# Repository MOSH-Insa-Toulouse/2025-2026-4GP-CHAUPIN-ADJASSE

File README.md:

##### **Promotion 2025-2026 Génie Physique INSA TOulouse** — *Marie-Charbel ADJASSE-ABENI & Baptiste CHAUPIN*
**Encadrants :** J. Grisolia, B. Mestre, A. Biganzoli, C. Crouzet

# Projet Capteur

Ce projet collaboratif a pour but de mettre en place une chaîne de mesure complète, autonome et connectée permettant de calibrer, caractériser et analyser en temps réel un capteur de déformation low-tech à base de graphite tracé sur papier. 

Le projet se base directement des travaux de *Lin, CW, Zhao, Z., Kim, J. et al. (2014)* publiés dans *Nature*, intitulés **"Pencil Drawn Strain Gauges and Chemiresistors on Paper"**.

### Contexte & Principe Physique

Le capteur est réalisé par dépôt de graphite sur une feuille de papier (épaisseur $0.35\text{ mm}$) à l'aide de différents crayons (B, 3B, 6B, 2H, HB). Ce dépôt forme un **système granulaire** dont la conductance dépend de la distance inter-grain :
* **En compression** : La distance inter-grain diminue, provoquant une augmentation de la conductance (chute de la résistance).
* **En traction/tension** : La distance augmente, entraînant une hausse de la résistance.

L'objectif de ce projet est de concevoir l'électronique d'acquisition, le système embarqué et l'interface applicative permettant de déduire fidèlement l'angle de flexion et la déformation du papier en fonction de sa résistance.

### Livrables du Projet
1. Un **Shield PCB personnalisé** pour Arduino UNO (mesure, amplification et communication).
2. Un **Code source Arduino (C++)** structuré en machine à états gérant l'acquisition et l'IHM.
3. Une **Application Android (.APK)** sous MIT App Inventor assurant la supervision et le tracé graphique en temps réel.
4. Une **Fiche technique (Datasheet)** de caractérisation du capteur en graphite.

### Composants Utilisés
* **Microcontrôleur :** Carte Arduino UNO Rev 3.
* **Amplification (AOP) :** LTC1050.
* **Passifs d'instrumentation :** Résistances ($2 \times 1\text{ k}\Omega$, $1 \times 10\text{ k}\Omega$, $2 \times 100\text{ k}\Omega$) & Condensateurs ($2 \times 100\text{ nF}$, $1 \times 1\text{ }\mu\text{F}$).
* **Rétroaction Numérique :** Potentiomètre digital SPI MCP41010 ($10\text{ k}\Omega$, $256$ pas).
* **Interface (IHM) :** Écran OLED 0.96" SSD1306 (I2C) & Encodeur rotatif Keyes KY-040.
* **Communication :** Module Bluetooth HC-05.
* **Comparaison avec un capteur disponible sur le marché :** Capteur de flexion commercial (Flex Sensor Flexpoint / LLC 1070) + Résistance de charge de $47\text{ k}\Omega$.

### Fonctionnalités Principales du Système

* **Auto-Calibration Dynamique (Asservissement)** : Compensation automatique de la résistance à plat ($R_0$) du capteur (de l'ordre du $\text{M}\Omega$) via un potentiomètre digital (MCP41010) afin de centrer la tension de repos à $V_{cc}/2$ ($2.5\text{V} \pm 2\%$).
* **Machine à États Finis (FSM)** : Architecture logicielle Arduino robuste structurée en 4 états distincts : `CALIBRATION`, `CHOIX_MENU`, `MESURE` et `AFFICHAGE`.
* **Interface Homme-Machine (IHM) Autonome** : Navigation par encodeur rotatif (gestion par interruptions) à travers des menus dynamiques affichés sur un écran OLED SSD1306 (I2C).
* **Supervision Mobile en Temps Réel** : Application Android dédiée (MIT App Inventor) affichant les graphiques de déformation, les indicateurs de stabilité et un module d'exportation de données scientifiques au format `.txt`.

---

### Simulation Électronique & Conditionnement (LTSpice)

Le capteur de graphite présente une résistance à vide très élevée (de l'ordre du $\text{M}\Omega$ au $\text{G}\Omega$ selon le crayon utilisé). Sous une alimentation de $5\text{V}$, le courant généré est de l'ordre du nanoampère ($\text{nA}$). Un étage d'amplification est indispensable pour adapter le signal à la dynamique du convertisseur analogique-numérique (ADC) de l'Arduino ($0 - 5\text{V}$).

### Circuit Amplificateur Transimpédance (LTC1050)
Pour exploiter le très faible courant traversant le capteur à haute résistance, un montage amplificateur transimpédance a été modélisé sur LTSpice. Le rapport signal/bruit est optimisé par **trois filtres passe-bas** :
1. **Filtre d'entrée (175 Hz)** : Élimine les vibrations mécaniques et tremblements parasites ($C_1 = 100\text{ nF}$, $R_1 = 100\text{ k}\Omega$, // $R_4 = 10\text{ k}\Omega$).
2. **Filtre actif de rétroaction (1.6 Hz)** : Atténue le bruit secteur de $50\text{ Hz}$ du réseau électrique ($C_3 = 1\text{ µF}$, $R_3 = 100\text{ k}\Omega$).
3. **Filtre de sortie (1.6 kHz)** : Élimine les parasites haute fréquence générés par l'électronique ($C_2 = 100\text{nF}$, $R_5 = 1\text{ k}\Omega$).

La fonction de transfert globale liant la tension mesurée par l'ADC ($V_{ADC}$) à la résistance du capteur ($R_c$) est régie par l'équation :

$$V_{ADC} = \left(1 + \frac{R_3}{R_2}\right) \cdot \frac{R_1}{R_1 + R_c + R_5} \cdot V_{cc}$$

D'où l'extraction mathématique de la résistance du capteur opérée par le firmware :

$$R_c = \left(1 + \frac{R_3}{R_2}\right) \cdot R_1 \cdot \frac{V_{cc}}{V_{ADC}} - R_1 - R_5$$

Note : La résistance $R_2$ est ajustée dynamiquement en modifiant l'indice du potentiomètre numérique MCP41010.

---

## Conception & Fabrication du Shield (KiCad)

Le circuit imprimé, conçu sous KiCad et fabriqué par gravure chimique (insolation UV + perchlorure de fer), se branche comme un Shield sur un Arduino Uno.

### Configuration des Broches (Pinout PCB)

| Composant | Rôle / Description | Interface / Broches Arduino |
| :--- | :--- | :--- |
| **AOP LTC1050** | Amplificateur de signal transimpédance | Entrée Analogique `A0` |
| **MCP41010** | Potentiomètre numérique (10 kΩ) | Bus SPI (`CS: D8` ou `D10`, `MOSI: D11`, `SCK: D13`) |
| **OLED 0.96"** | Écran d'affichage I2C (SSD1306) | Bus I2C (`SDA: A4`, `SCL: A5`) |
| **Encodeur** | Navigation dans le menu déroulat de l'écran OLED | Interruptions (`CLK: D2`, `DT: D4`, `SW: D5` ou `D6`) |
| **HC-05 / HC-06** | Module de communication Bluetooth | SoftwareSerial (`RX: D5` ou `D8`, `TX: D3` ou `D7`) |
| **Flex Sensor** | Capteur commercial de comparaison | Pont diviseur de tension ($47\text{ k}\Omega$) |

Un **plan de masse (GND)** étendu a été configuré sur la face cuivre pour stabiliser les potentiels analogiques et atténuer la diaphonie induite par les transmissions RF du Bluetooth.

### Modifications Matérielles
Pendant la phase de test du PCB, une correction majeures ont été apportées :
2. **Routage du MCP41010 Révisé** : Le potentiomètre avait d'abord été configuré selon la 1ère démonstration des TD MOSH. 

Cathy a alors réussi à réparer le coup en ajoutant des fils et rayant des pistes de cuivre.

---

### Architecture Logicielle : Machine à États (Arduino)

Le microcontrôleur exécute un algorithme structuré sous forme d'une **Machine à États** pour orchestrer la synchronisation temporelle des tâches.

       [ START ]
           │
           ▼
    ┌──────────────┐
    │ CALIBRATION  │ ───► (Ajuste R2 pour centrer V_A0 à 2.5V)
    └──────┬───────┘
           │ (Équilibre atteint)
           ▼
    ┌──────────────┐
    │  CHOIX_MENU  │ ◄───┐ (Sélection via l'encodeur rotatif)
    └──────┬───────┘     │
           │ (Clic SW)   │ (Clic SW pour quitter)
           ▼             │
    ┌──────────────┐     │
    │ MESURE & AFF │ ────┘ (Transmission Bluetooth 5Hz & OLED)
    └──────────────┘

---

## Interface de Supervision Mobile (MIT App Inventor)

L'application Android sert d'interface de supervision graphique et d'unité d'archivage des mesures.

### Logique Interne des Blocs
1. **Initialisation de la communication ave arduino** : Gestion par voyant et liste pour la connection au module bluetooth.
2. **Gestion de l'Horloge** : La routine cyclique est calée sur un paramètre `TimerInterval` fixe de $200\text{ ms}$ ($5\text{ Hz}$). Dès que l'instruction `BytesAvailableToReceive > 0` est validée, le flux de texte est capturé.
3. **Tracé Dynamique Automatisé** : Le moteur graphique applique un algorithme de défilement horizontal continu sur un composant `Canvas` en stockant la coordonnée $X_{courant}$ et en reliant la coordonnée $Y_{precedent}$ à la valeur rafraîchie, assurant un rendu en temps réel de la déformation.
4. **Enregistrement et Exportation** : Un bloc concatène en continu l'ensemble des mesures dans une variable de type chaîne (`global historique`) intercalée par des sauts de ligne (`\n`) et des points-virgules (`;`). L'appui sur le bouton d'exportation appelle le gestionnaire `File1.SaveFile` pour inscrire le document sous la forme `/MesureGraphene.txt` directement dans l'arborescence physique du téléphone. Cette dernière option n'est malheureuseent pas fonctionnelle (difficulté à trouver l'arborescence exacte sur les téléphones portables).

---

## Banc de Test & Métrologie Expérimentale

Pour calibrer le capteur en graphite, l'équipe a développé un banc de test étagé conçu sur mesure par impression 3D (rayons de courbure étalonnés de $1\text{ cm}$ à $2.5\text{ cm}$ avec des pas de $0.25\text{ cm}$).

### Configuration Mécanique : Traction vs Compression
La fixation mécanique sur les cylindres de calibration s'effectue via des pinces de test Mueller connectées aux zones de contact du film de graphite :
* **Mode Extension / Traction (Tension)** : Le film en U de graphite est orienté vers l'extérieur (face à l'opérateur). La flexion étire mécaniquement le maillage, augmentant la distance inter-grain de la couche de carbone, ce qui induit une élévation de la résistance globale ($R_{capt} \uparrow$).

* **Mode Compression** : Le capteur est retourné face blanche apparente, la couche active de graphite étant plaquée directement contre la structure cylindrique du gabarit vert. La courbure comprime les feuillets de graphite, réduisant la barrière tunnel inter-particulaire et provoquant une baisse de la résistance électrique ($R_{capt} \downarrow$).

### Synthèse des Résultats Métrologiques (Datasheet)
Les essais ont permis de comparer les facteurs de jauge (sensibilité $K$) et la répétabilité en fonction de la texture du crayon employé (2H, HB, 2B, 4B, 6B) :
* **Mines Tendres (Crayon 6B)** : Très haute teneur en carbone pur, offrant une excellente conductivité initiale et une très bonne linéarité de la variation relative de résistance en compression. Cependant, la cohésion mécanique est faible, entraînant une perte de matière rapide par friction.
* **Mines Dures (Crayons B et 3B)** : Proportion plus importante de liant argileux. La résistance de base est plus élevée, ce qui génère une sensibilité transimpédance plus nerveuse (facteur de jauge supérieur), mais le signal est sujet à une dérive exponentielle et à des irrégularités, illustrant parfaitement la théorie des milieux granulaires désordonnés.

---

## Conclusion Générale & Perspectives

Ce projet a permis de valider avec succès le développement et l'instrumentation d'une chaîne de mesure **Low-Tech complète et connectée**, de la modélisation analogique à l'application mobile de traitement.

### Évaluation du Potentiel d'Industrialisation
**Avantages** : Coût matière nul, éco-conception évidente, accessibilité universelle, excellente réponse en traction/compression, faible consommation électrique et capteur remplaçable ou réparable instantanément sur le terrain en ré-appliquant du graphite.
**Limitations** : Faible répétabilité due à l'usure mécanique du film (perte de graphite au fil des flexions), instabilité des points de contact des pinces et hystérésis structurelle du support en papier face aux jauges industrielles en polymère kapton.

### Améliorations pour une Viabilité Industrielle
Pour transformer ce démonstrateur en un produit industriellement viable (ex : capteurs jetables à bas coût pour l'analyse ponctuelle de structures ou dispositifs éducatifs), les axes de recherche suivants sont préconisés :
1. **Électrodes de Contact Fixes** : Remplacer la connexion mécanique directe par l'impression de plots permanents pour figer le contact.
2. **Protection des matériaux** : Appliquer une fine couche de plastification ou un vernis protecteur isolant sur le film de graphite afin de figer les grains de carbone. Appliquer un vernis sur le PCB afin d'éviter l'oxydation des pistes de cuivre.

---

## 👥 9. Contacts & Collaborations

Pour toute demande d'information complémentaire ou consultation des fichiers de fabrication vous pouvez contacter l'équipe projet de l'**INSA Toulouse** :

### Équipe Étudiants
* **Marie-Charbel ADJASSE-ABENI** : `adjasse-aben@insa-toulouse.fr`
* **Baptiste CHAUPIN** : `chaupin@insa-toulouse.fr`

### Équipe Enseignants
* **Jérémie Grisolia** (Enseignant-Chercheur, LAAS-CNRS / INSA) : `jeremie.grisolia@insa-toulouse.fr`
* **Benjamin Mestre** (Ingénieur d'Études Électroniques, Scalian) : `benjamin.mestre@scalian.com`
* **Arnauld Biganzoli** (Responsable Instrumentation, INSA) : `arnauld.biganzoli@insa-toulouse.fr`
* **Cathy Crouzet** (Technicienne d'Atelier de Fabrication PCB, INSA) : `crouzet@insa-toulouse.fr`

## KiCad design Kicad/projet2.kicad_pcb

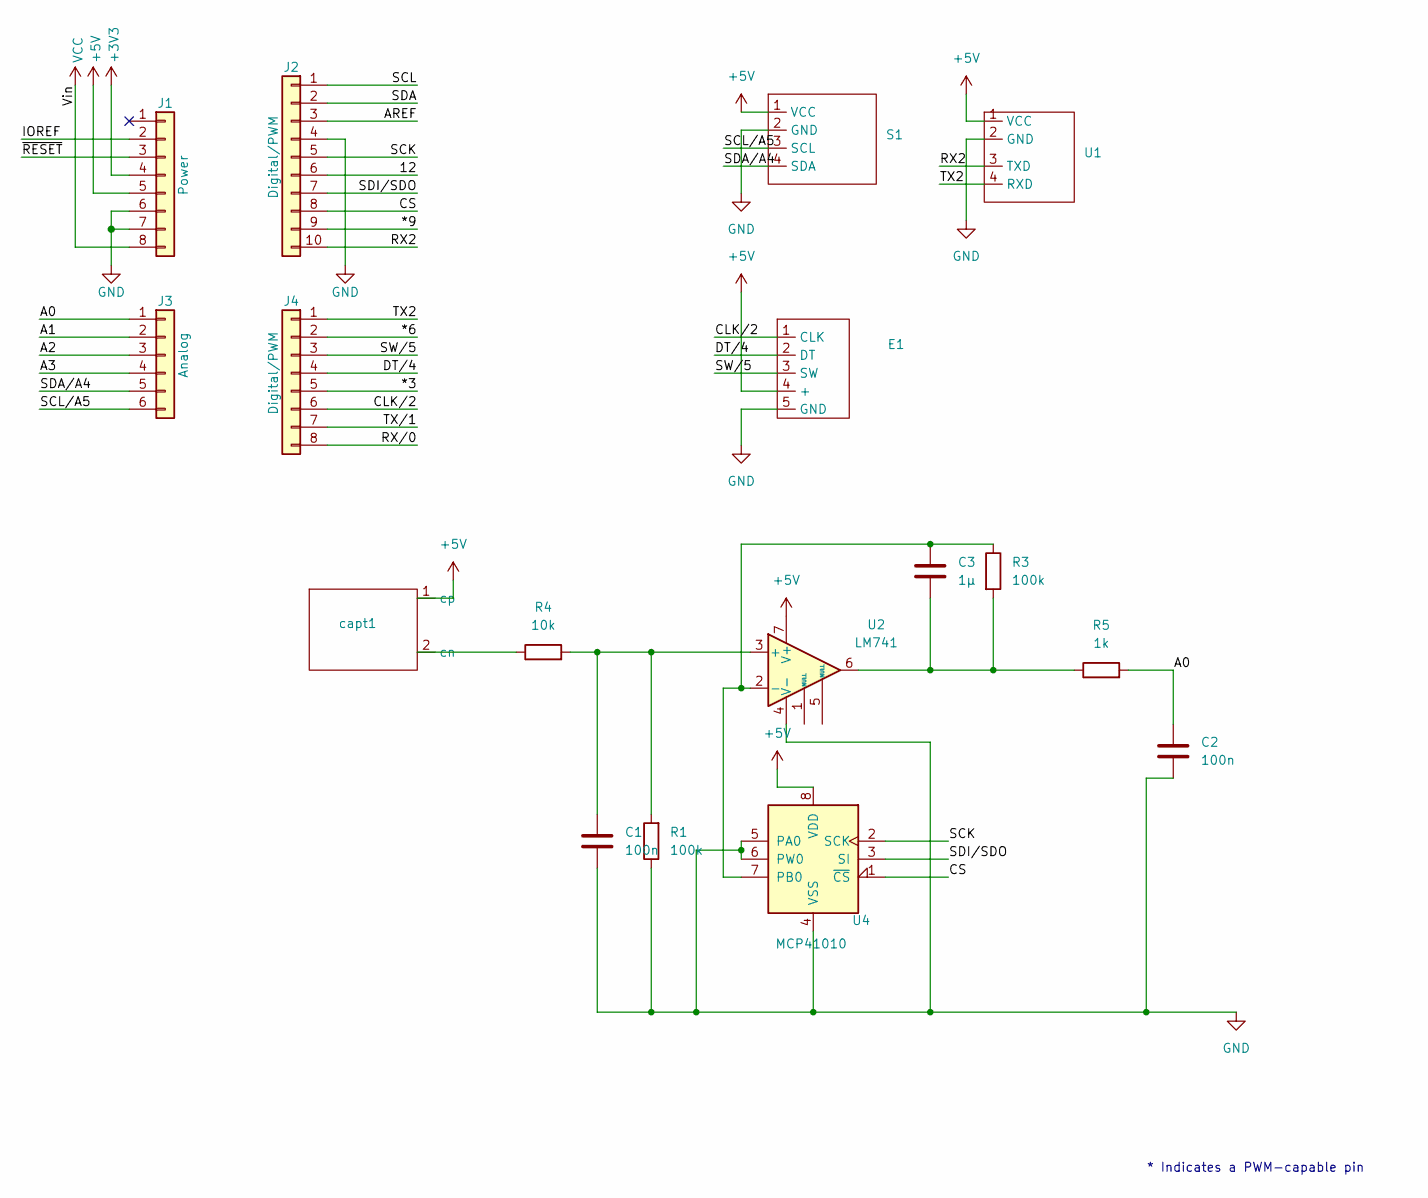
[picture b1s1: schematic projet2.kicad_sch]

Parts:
C1: 100n; C1
C2: 100n; C2
C3: 1µ; C3
E1: Encodeur
J1: Power; PinSocket_1x08_P2.54mm_Vertical
J2: Digital/PWM; PinSocket_1x10_P2.54mm_Vertical
J3: Analog; PinSocket_1x06_P2.54mm_Vertical
J4: Digital/PWM; PinSocket_1x08_P2.54mm_Vertical
R1: 100k; R1
R3: 100k; R3
R4: 10k; R4
R5: 1k; R5
S1: OLed
U1: Bluetooth
U2: LM741; LTC1050
U4: MCP41010
capt1: CAPTEUR

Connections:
+3V3: J1.4
+5V: E1.4 (+), J1.5, S1.1 (VCC), U1.1 (VCC), U2.7 (V+), U4.8 (VDD), capt1.1 (cp)
/12: J2.6
/*3: J4.5
/*6: J4.2
/*9: J2.9
/A0: C2.1, J3.1, R5.2
/A1: J3.2
/A2: J3.3
/A3: J3.4
/AREF: J2.3
/CLK/2: E1.1 (CLK), J4.6
/CS: J2.8, U4.1 (~CS)
/DT/4: E1.2 (DT), J4.4
/IOREF: J1.2
/RX2: J2.10, U1.3 (TXD)
/RX/0: J4.8
/SCK: J2.5, U4.2 (SCK)
/SCL: J2.1
/SCL/A5: J3.6, S1.3 (SCL)
/SDA: J2.2
/SDA/A4: J3.5, S1.4 (SDA)
/SDI/SDO: J2.7, U4.3 (SI)
/SW/5: E1.3 (SW), J4.3
/TX2: J4.1, U1.4 (RXD)
/TX/1: J4.7
/~RESET: J1.3
GND: C1.2, C2.2, E1.5 (GND), J1.6, J1.7, J2.4, R1.1, S1.2 (GND), U1.2 (GND), U2.4 (V-), U4.4 (VSS), U4.5 (PA0), U4.6 (PW0)
unnamed: C3.2, R3.2, R5.1, U2.6
unnamed: C1.1, R1.2, R4.2, U2.3 (+)
unnamed: C3.1, R3.1, U2.2 (-), U4.7 (PB0)
unnamed: R4.1, capt1.2 (cn)
VCC: J1.8

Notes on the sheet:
* Indicates a PWM-capable pin

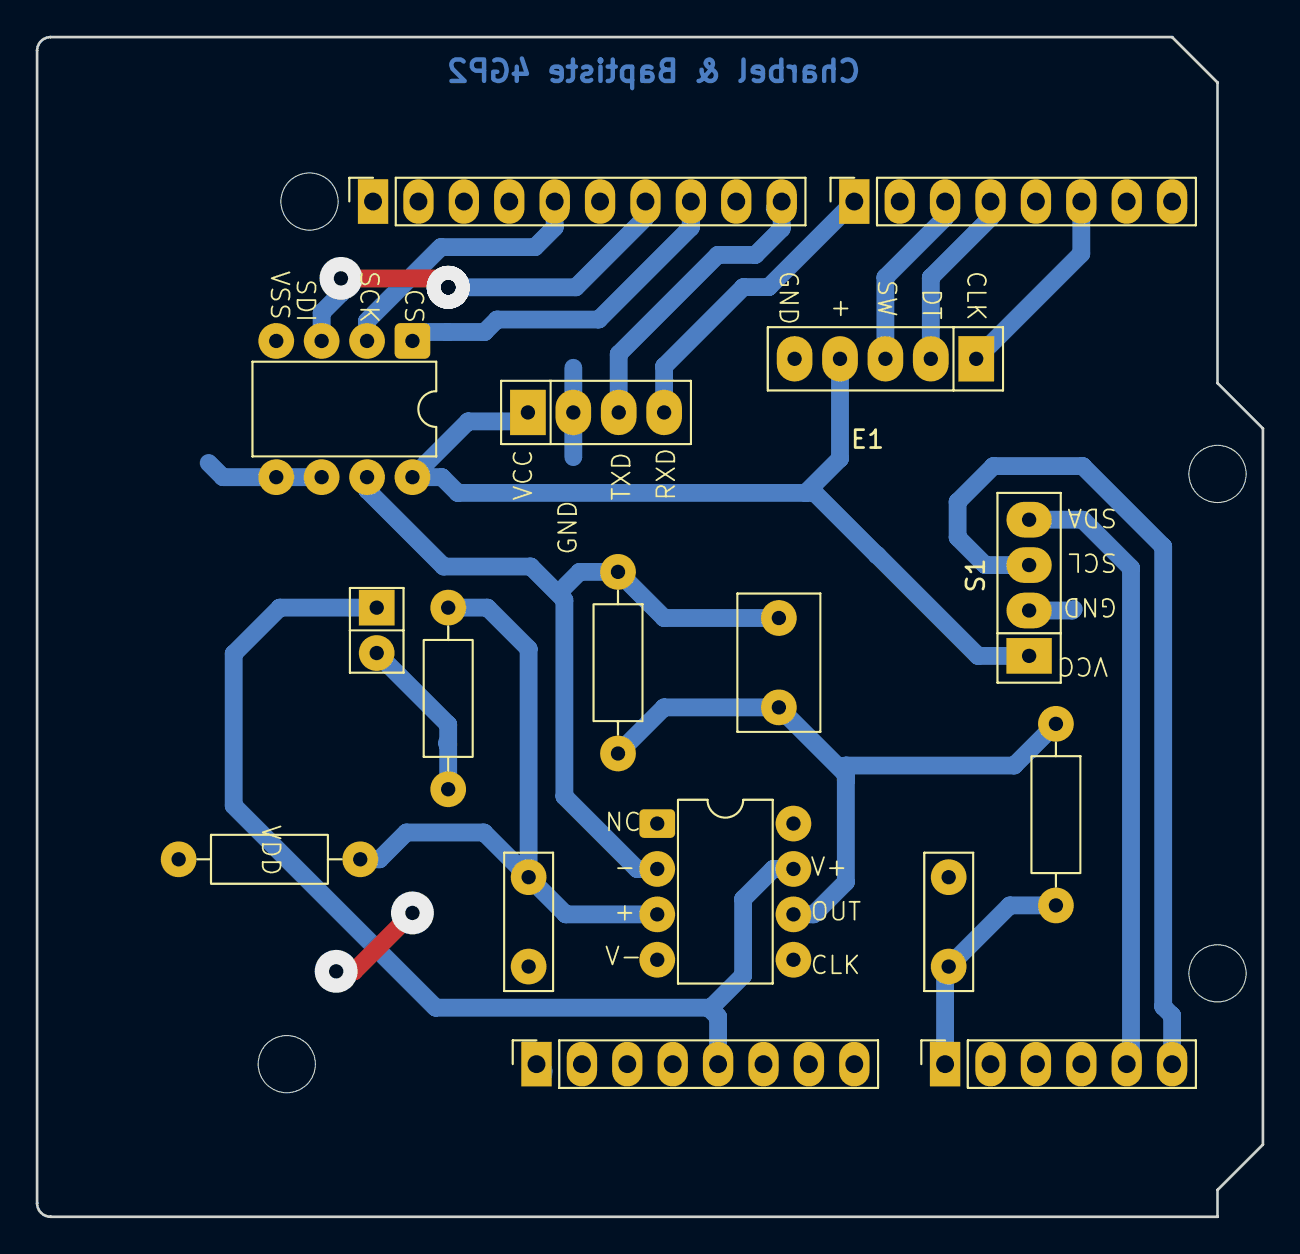
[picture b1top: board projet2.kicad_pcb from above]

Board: 2 copper layers, 68.6 x 66.0 mm, 21 parts (0 on the bottom side), 17 nets.

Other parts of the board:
MH1, MH2, MH3, MH4: MountingHole_3.2mm

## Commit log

2026-02-10 création du projet
2026-02-10 création nouveau projet
2026-05-24 Update README.md
    Il manque les captures d'écran et quelques explications
2026-05-28 Create description
2026-05-28 Create desc
2026-05-28 Create descr
